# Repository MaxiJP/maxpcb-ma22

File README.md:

# maxpcb-ma22
 basically jus the ai03 keeb xD

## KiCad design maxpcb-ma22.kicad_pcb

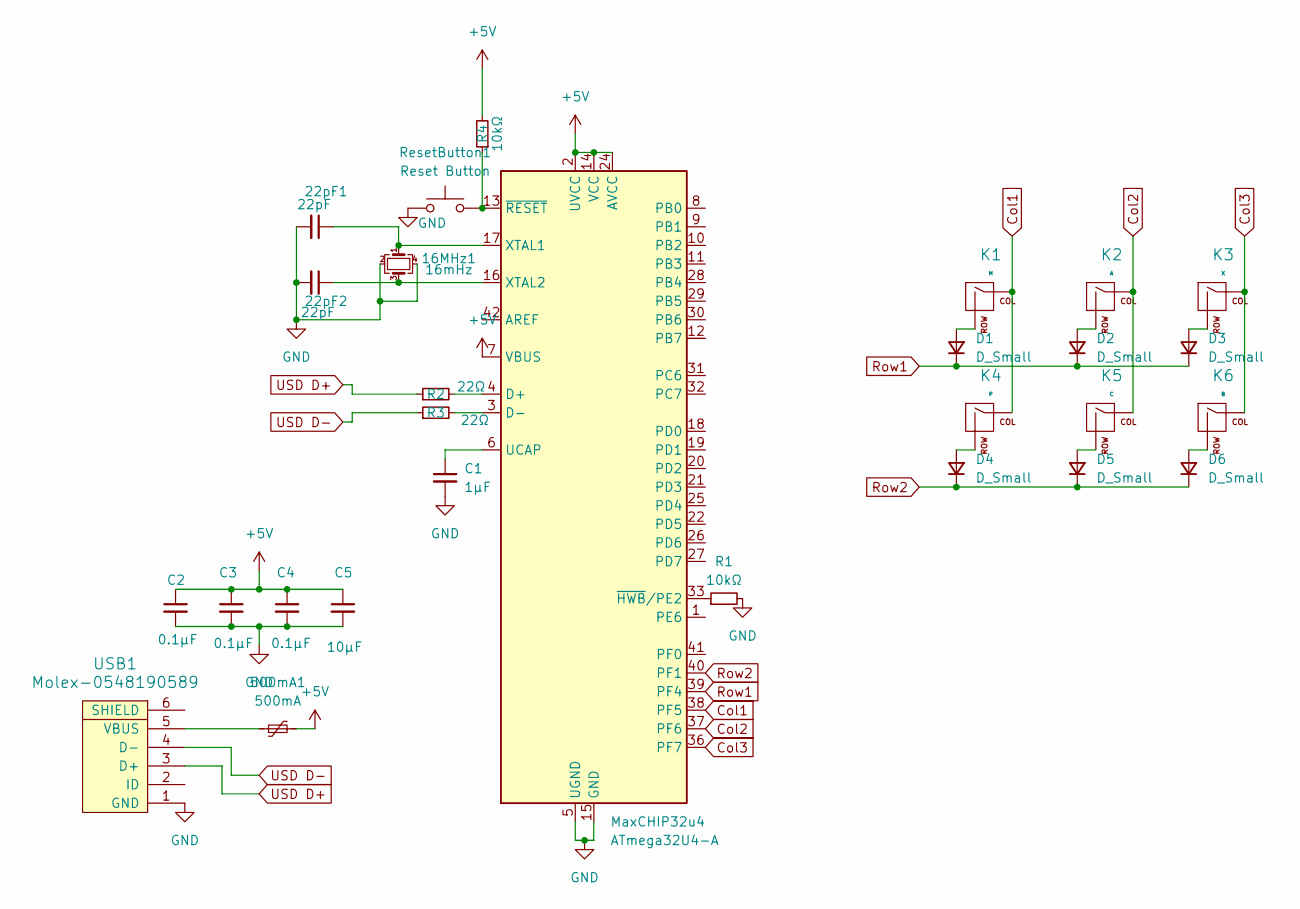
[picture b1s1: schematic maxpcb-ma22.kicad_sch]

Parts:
16MHz1: 16mHz; Crystal_SMD_3225-4Pin_3.2x2.5mm
22pF1, 22pF2: 22pF; C_0805_2012Metric
500mA1: 500mA; Fuse_1206_3216Metric
C1: 1µF; C_0805_2012Metric
C2, C3, C4: 0.1µF; C_0805_2012Metric
C5: 10µF; C_0805_2012Metric
D1, D2, D3, D4, D5, D6: D_Small; D_SOD-123
K1: M; MXOnly-1U
K2: A; MXOnly-1U-NoLED
K3: X; MXOnly-1U-NoLED
K4: P; MXOnly-1U-NoLED
K5: C; MXOnly-1U-NoLED
K6: B; MXOnly-1U-NoLED
MaxCHIP32u4: ATmega32U4-A; TQFP-44_10x10mm_P0.8mm
R1, R4: 10kΩ; R_0805_2012Metric
R2, R3: 22Ω; R_0805_2012Metric
ResetButton1: Reset Button; SKQG-1155865
USB1: Molex-0548190589

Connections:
+5V: 500mA1.2, C2.1, C3.1, C4.1, C5.1, MaxCHIP32u4.2 (UVCC), MaxCHIP32u4.7 (VBUS), MaxCHIP32u4.14 (VCC), MaxCHIP32u4.24 (AVCC), MaxCHIP32u4.34 (VCC), MaxCHIP32u4.44 (AVCC), R4.2
Col1: K1.1 (COL), K4.1 (COL), MaxCHIP32u4.38 (PF5)
Col2: K2.1 (COL), K5.1 (COL), MaxCHIP32u4.37 (PF6)
Col3: K3.1 (COL), K6.1 (COL), MaxCHIP32u4.36 (PF7)
GND: 16MHz1.2, 16MHz1.4, 22pF1.2, 22pF2.2, C1.2, C2.2, C3.2, C4.2, C5.2, MaxCHIP32u4.5 (UGND), MaxCHIP32u4.15 (GND), MaxCHIP32u4.23 (GND), MaxCHIP32u4.35 (GND), MaxCHIP32u4.43 (GND), R1.2, ResetButton1.1, USB1.1 (GND); also elsewhere on the board
unnamed: D1.2 (A), K1.2 (ROW)
unnamed: D2.2 (A), K2.2 (ROW)
unnamed: D3.2 (A), K3.2 (ROW)
unnamed: D4.2 (A), K4.2 (ROW)
unnamed: D5.2 (A), K5.2 (ROW)
unnamed: D6.2 (A), K6.2 (ROW)
unnamed: MaxCHIP32u4.4 (D+), R2.2
unnamed: MaxCHIP32u4.3 (D-), R3.2
unnamed: C1.1, MaxCHIP32u4.6 (UCAP)
unnamed: 16MHz1.1, 22pF1.1, MaxCHIP32u4.17 (XTAL1)
unnamed: 16MHz1.3, 22pF2.1, MaxCHIP32u4.16 (XTAL2)
unnamed: MaxCHIP32u4.33 (~HWB/PE2), R1.1
unnamed: MaxCHIP32u4.13 (~RESET), R4.1, ResetButton1.2
unnamed 18: 500mA1.1, USB1.5 (VBUS); also elsewhere on the board
Row1: D1.1 (K), D2.1 (K), D3.1 (K), MaxCHIP32u4.39 (PF4)
Row2: D4.1 (K), D5.1 (K), D6.1 (K), MaxCHIP32u4.40 (PF1)
USD D+: R2.1, USB1.3 (D+); also elsewhere on the board
USD D-: R3.1, USB1.4 (D-); also elsewhere on the board

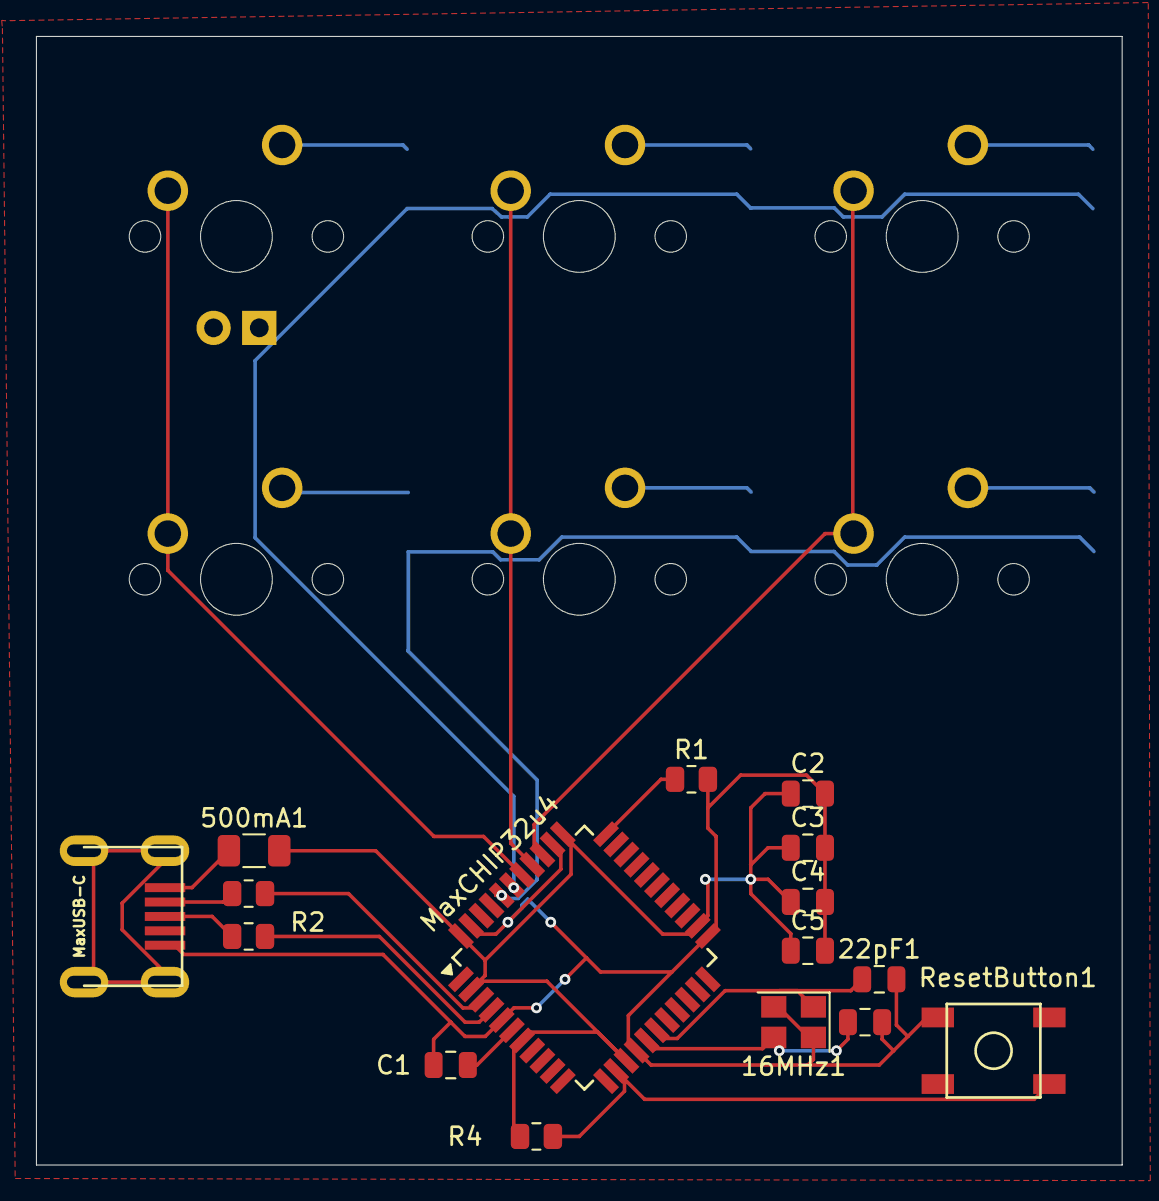
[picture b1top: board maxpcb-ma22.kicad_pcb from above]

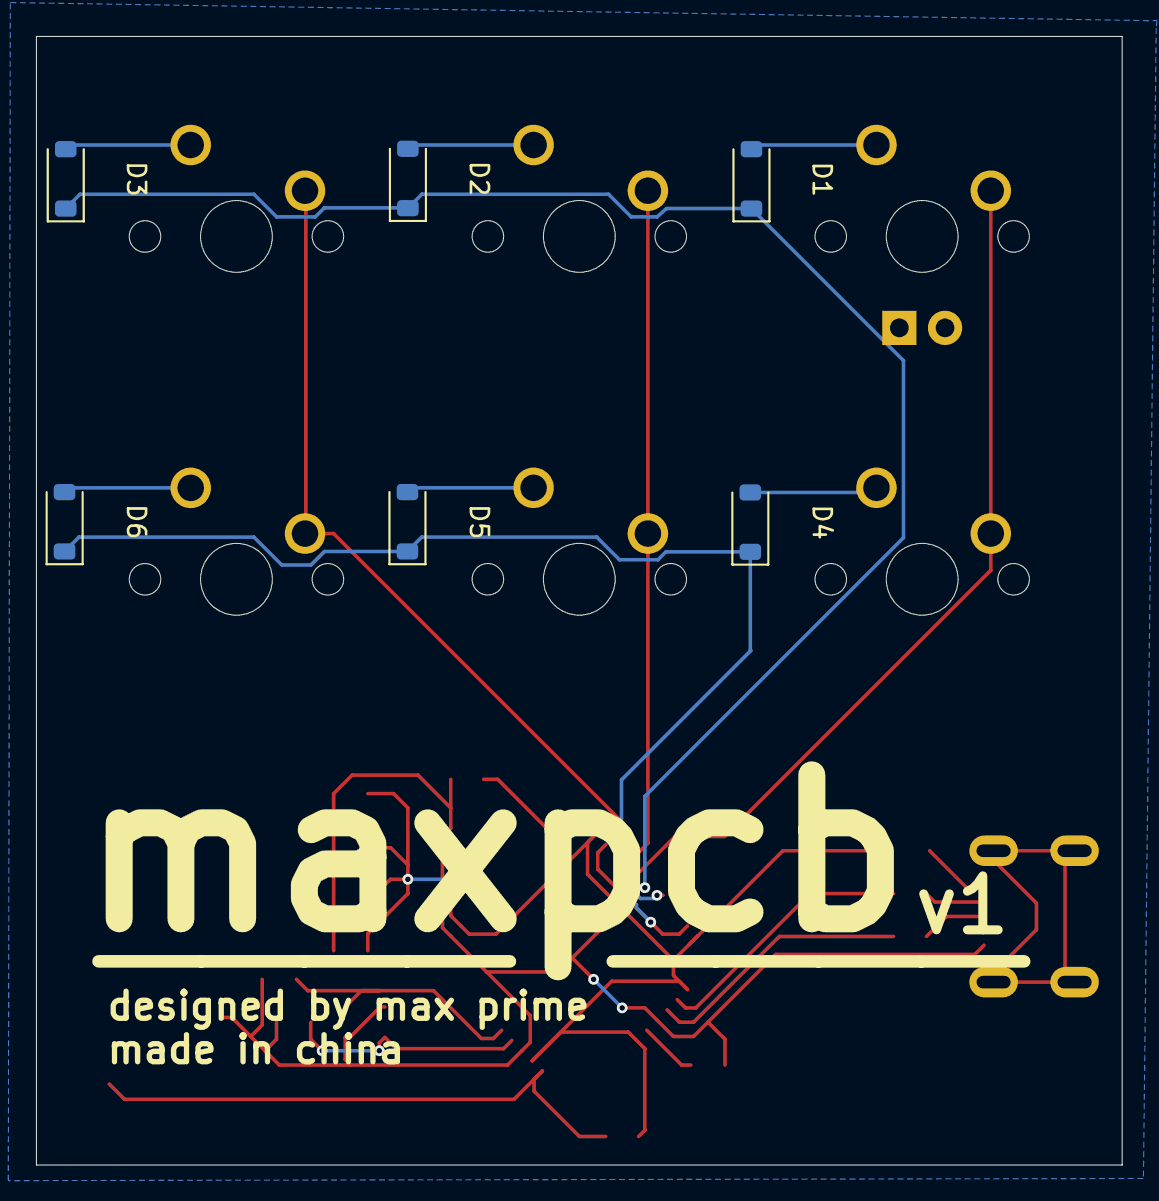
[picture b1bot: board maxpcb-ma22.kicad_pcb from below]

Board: 2 copper layers, 60.3 x 62.7 mm, 28 parts (6 on the bottom side), 23 nets.

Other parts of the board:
MaxUSB-C: Molex-0548190589

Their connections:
GND: MaxUSB-C.1 (GND); also elsewhere on the board
unnamed 18: MaxUSB-C.5 (VBUS); also elsewhere on the board
USD D+: MaxUSB-C.3 (D+); also elsewhere on the board
USD D-: MaxUSB-C.4 (D-); also elsewhere on the board

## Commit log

2024-03-06 init
2024-03-06 Adding in some submodules of resources
2024-03-06 Adding libraries
2024-03-06 Schematic
2024-03-09 complete redo with 32u4
